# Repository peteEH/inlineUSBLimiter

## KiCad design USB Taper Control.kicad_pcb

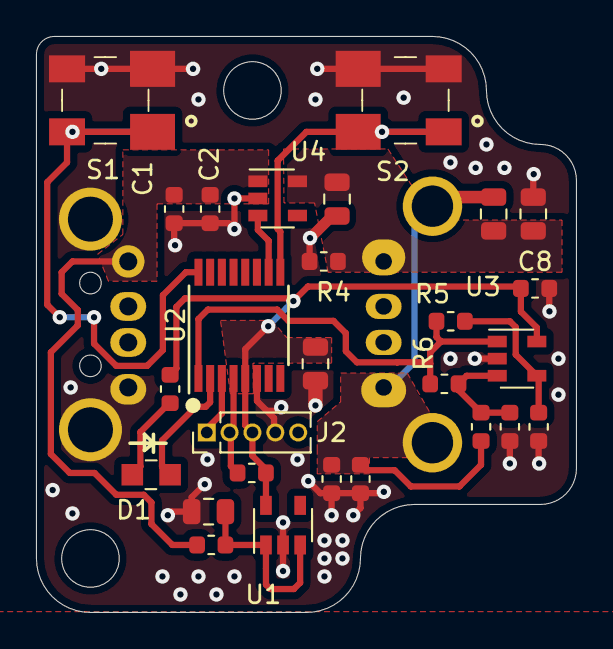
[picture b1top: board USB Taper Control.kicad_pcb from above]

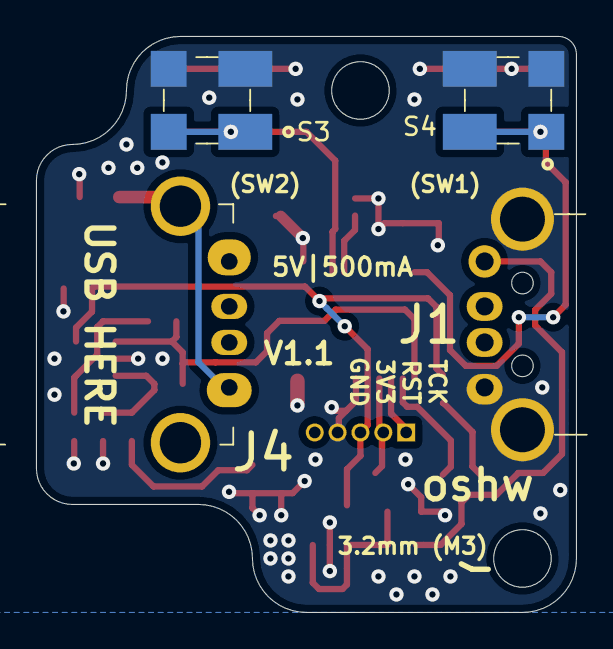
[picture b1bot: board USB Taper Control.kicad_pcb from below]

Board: 2 copper layers, 30.0 x 32.0 mm, 31 parts (4 on the bottom side), 16 nets.

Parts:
C1, C2: 220nF|0603; C_0603_1608Metric
C3, C5: 4.7uF|0805; C_0805_2012Metric
C4: 1uF|0805; C_0805_2012Metric
C6, C8: 2.2uF|0603; C_0603_1608Metric
C7, C11: 22uF|0805; C_0805_2012Metric
D1: LG_R971-KN-1; 0805
J1: UP2-AH-1-TH; USB_Male_A_UP2-AH-1-TH
J2: Conn_01x05; PinHeader_1x05_P1.27mm_Vertical
J4: UE27AC54100; USB_A_Female_UE27AC54100
R1: 47K|0603; R_0603_1608Metric
R2, R4, R7, R10: 1K|0603; R_0603_1608Metric
R3: 2|0603; R_0603_1608Metric
R5: 15K|0603; R_0603_1608Metric
R6: 0|0603; R_0603_1608Metric
R8, R9: 0.1|0603; R_0603_1608Metric
S1, S2, S3, S4: PTS 647 SK38 SMTR2 LFS; Switch_Tactile_SMD_4.5x4.5mm_TL3315NF160Q
U1: TPS76933; SOT-23-5
U2: MSP430FR2110IPW16R; TSSOP-16_4.4x5mm_P0.65mm
U3: LPV811DBV; SOT-23-5
U4: MAX40200AUK; SOT-23-5

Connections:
+3V3: C5.1, C8.1, J2.3, R1.1, R2.1, U1.5, U2.5, U3.5
+5V: C1.1, C2.1, J1.1, R3.1, U4.1
/CURR_FILT: R5.2, R6.2, U2.1, U3.1
/RST: J2.2, R1.2, U2.4
/TCK: J2.1, U2.3
/USB_PWR_OUT: C4.1, C7.1, C11.1, J4.1, R4.1, U4.5
GND: C1.2, C2.2, C3.2, C4.2, C5.2, C6.2, C8.2, C11.2, J1.4, J1.SH, J2.4, R4.2, R8.2, R9.2, R10.1, S1.3, S1.4, S2.3, S2.4, S3.3, S3.4, S4.3, S4.4, U1.2, U2.6, U3.2, U4.2
ISNS: C6.1, R6.1, R7.2, U3.3
unnamed: C3.1, R3.2, U1.1, U1.3
unnamed: C7.2, J4.4, J4.SH, R7.1, R8.1, R9.1
unnamed: D1.1, R2.2
unnamed: D1.2, U2.2
unnamed: R5.1, R10.2, U3.4
unnamed: S1.1, S1.2, S4.1, S4.2, U2.16
SW2: S2.1, S2.2, S3.1, S3.2, U2.9
USB_ENABLE: U2.10, U4.3

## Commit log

2021-08-01 init
2021-08-01 sw code
    msp430fr2111
